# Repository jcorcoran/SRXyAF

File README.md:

# SRXyAF
TalonSRX / Spark MAX breakout board

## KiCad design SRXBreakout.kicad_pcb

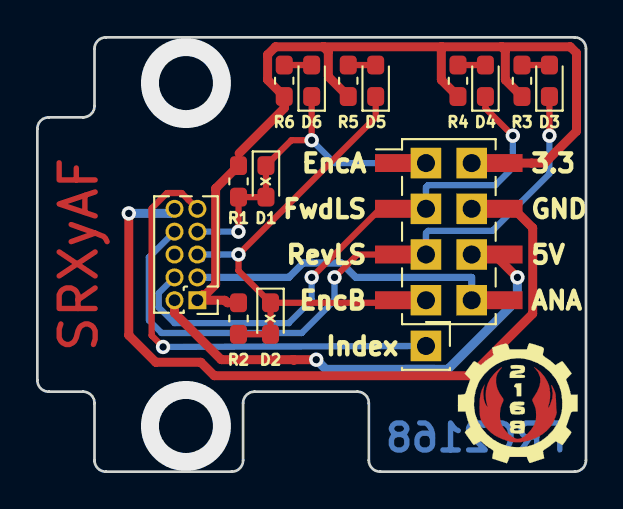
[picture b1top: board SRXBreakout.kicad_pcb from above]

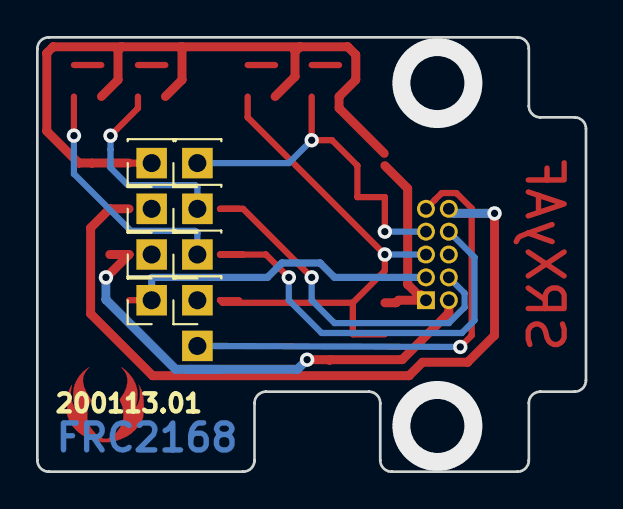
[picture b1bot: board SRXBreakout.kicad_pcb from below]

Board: 2 copper layers, 30.5 x 24.1 mm, 25 parts (8 on the bottom side), 13 nets.

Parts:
D1, D2: D_Schottky; D_0603_1608Metric_Pad1.05x0.95mm_HandSolder
D3, D4, D5, D6: LED; D_0603_1608Metric_Pad1.05x0.95mm_HandSolder
J1: Conn_02x05_Odd_Even; PinHeader_2x05_P1.27mm_Vertical
J2: Conn_02x04_Odd_Even; PinHeader_2x04_P2.54mm_Vertical_SMD
R1, R2: 10K; R_0603_1608Metric_Pad1.05x0.95mm_HandSolder
R3, R4, R5, R6: 390; R_0603_1608Metric_Pad1.05x0.95mm_HandSolder
TP1, TP2, TP3, TP4, TP5, TP6, TP7, TP8, TP9: TestPoint; PinSocket_1x01_P2.54mm_Vertical
Wings: LOGO; gear_small_wings-cu
Wings#2: LOGO; gear_small_wings-f.mask

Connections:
3.3V: J1.1, J2.2, R1.1, R2.2, R3.2, R4.2, R5.2, R6.2, TP4.1
5V: J1.2, J2.6, TP8.1
AnalogInput: J1.3, J2.8, TP9.1
FwdLim: D4.1, J1.4, J2.3, TP6.1
GND: J1.10, J2.4, TP5.1
unnamed: D3.2, R3.1
unnamed: D4.2, R4.1
unnamed: D5.2, R5.1
unnamed: D6.2, R6.1
QuadIndex: J1.9, TP1.1
QuadratureA: D1.1, D1.2, D6.1, J1.7, J2.1, R1.2, TP2.1
QuadratureB: D2.1, D2.2, D5.1, J1.5, J2.7, R2.1, TP3.1
RevLim: D3.1, J1.8, J2.5, TP7.1

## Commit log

2020-01-13 Add status LEDs, switch to 0603 parts, add tab for SPARK Max zip tie
2020-02-23 added manufacturing files. Updated schematic with as built component values
